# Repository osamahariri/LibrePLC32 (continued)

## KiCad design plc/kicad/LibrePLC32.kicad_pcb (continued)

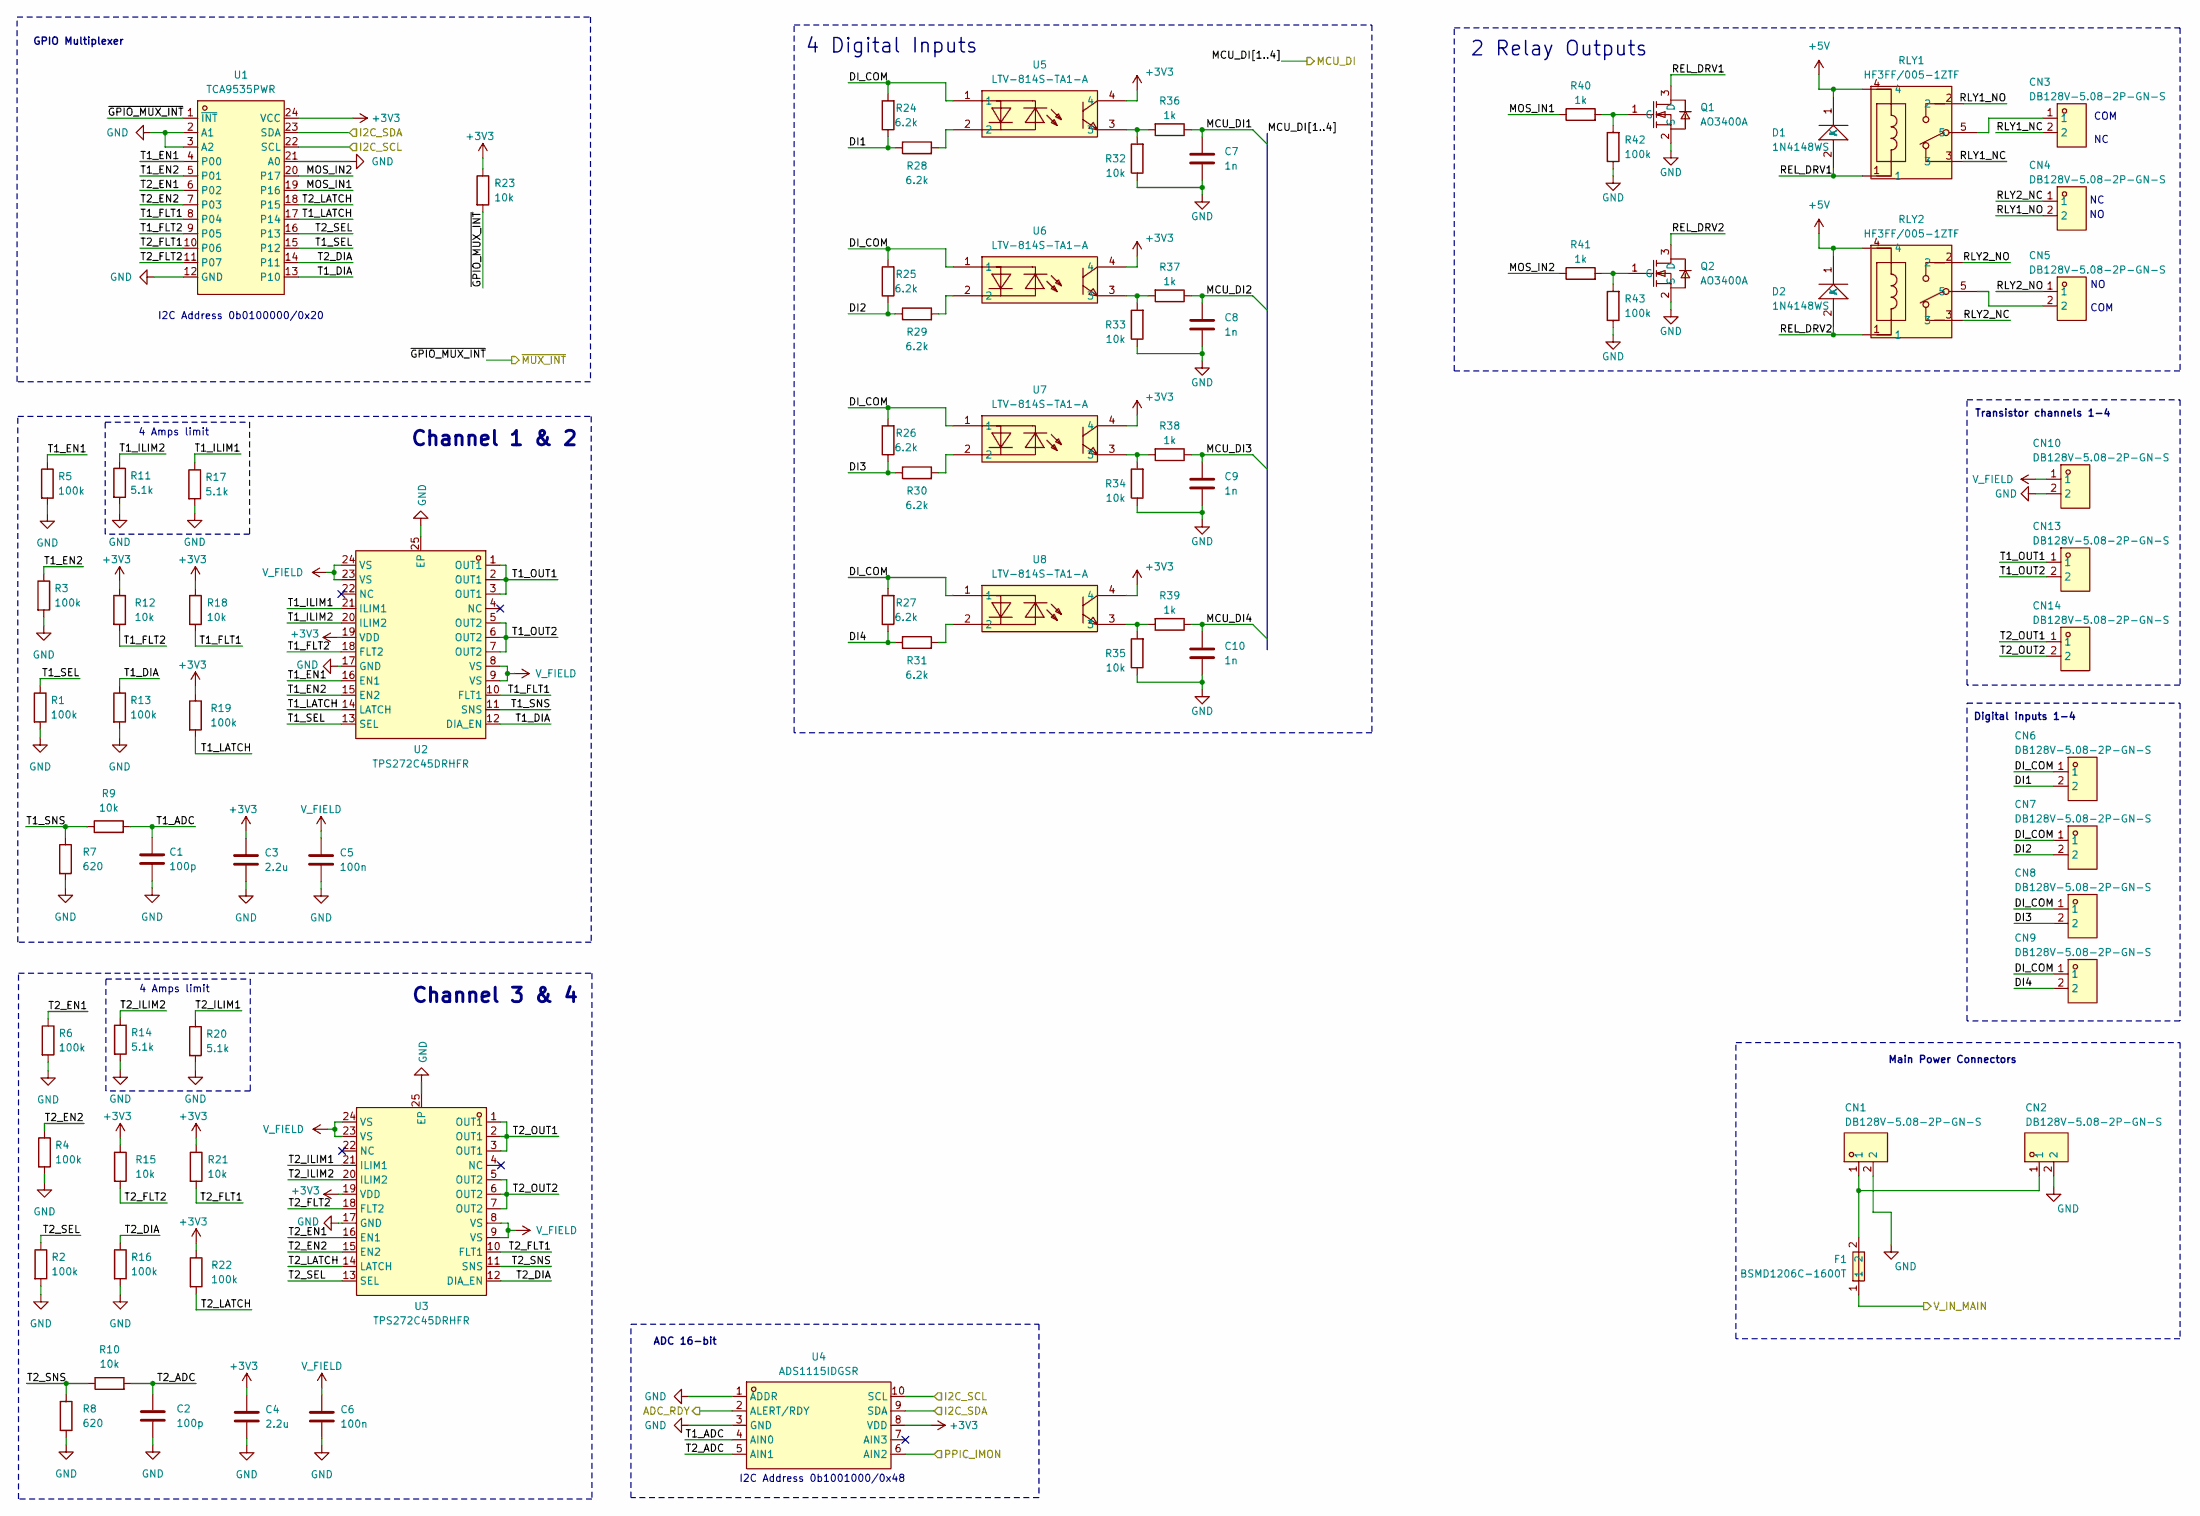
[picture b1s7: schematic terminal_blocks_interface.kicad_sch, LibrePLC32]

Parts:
C1, C2: 100p; C_0603_1608Metric
C3, C4: 2.2u; C_0603_1608Metric
C5, C6: 100n; C_0603_1608Metric
C7, C8, C9, C10: 1n; C_0603_1608Metric
CN1, CN2, CN3, CN4, CN5, CN6, CN7, CN8, CN9, CN10, CN13, CN14: DB128V-5.08-2P-GN-S; CONN-TH_2P-P5.08_DIBO_DB128V-5.08; MPN DB128V-5.08-2P-GN-S; LCSC Part C2915639
D1, D2: 1N4148WS; SOD-323_L1.8-W1.3-LS2.7-RD; MPN 1N4148WS-E3-08; LCSC Part C129905
F1: BSMD1206C-1600T; F1206; MPN BSMD1206C-1600T; LCSC Part C49328461
Q1, Q2: AO3400A; SOT-23-3_L2.9-W1.3-P1.90-LS2.4-BR; MPN AO3400A; LCSC Part C42419946
R1, R2, R3, R4, R5, R6, R13, R16, R19, R22, R42, R43: 100k; R_0603_1608Metric
R7, R8: 620; R_0603_1608Metric
R9, R10, R12, R15, R18, R21, R23, R32, R33, R34, R35: 10k; R_0603_1608Metric
R11, R14, R17, R20: 5.1k; R_0603_1608Metric
R24, R25, R26, R27, R28, R29, R30, R31: 6.2k; R_0603_1608Metric
R36, R37, R38, R39, R40, R41: 1k; R_0603_1608Metric
RLY1, RLY2: HF3FF/005-1ZTF; RELAY-TH_HF3FF-018-1ZT; MPN HF3FF/005-1ZTF; LCSC Part C2764967
U1: TCA9535PWR; TSSOP-24_L7.8-W4.4-P0.65-LS6.4-BL; MPN TCA9535PWR(UMW); LCSC Part C22396388
U2, U3: TPS272C45DRHFR; VQFN-24_L5.0-W4.0-P0.50-BL-EP-1; MPN TPS272C45DRHFR; LCSC Part C3219943
U4: ADS1115IDGSR; MSOP-10_L3.0-W3.0-P0.50-LS5.0-BL; MPN ADS1115IDGSR; LCSC Part C37593
U5, U6, U7, U8: LTV-814S-TA1-A; OPTO-SMD-4_L4.6-W6.5-P2.54-LS10.3-BL; MPN LTV-814S-TA1-A; LCSC Part C108051

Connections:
+3V3: C3.1, C4.1, R12.1, R15.1, R18.1, R19.1, R21.1, R22.1, R23.1, U1.24 (VCC), U2.19 (VDD), U3.19 (VDD), U4.8 (VDD), U5.4, U6.4, U7.4, U8.4; also elsewhere on the board
+5V: D1.1 (K), D2.1 (K), RLY1.4, RLY2.4; also elsewhere on the board
/MCU/ADC_RDY: U4.2 (ALERT/RDY); also elsewhere on the board
/MCU/I2C_SCL: U1.22 (SCL), U4.10 (SCL); also elsewhere on the board
/MCU/I2C_SDA: U1.23 (SDA), U4.9 (SDA); also elsewhere on the board
/MCU/MCU_DI1: C7.1, R36.1; also elsewhere on the board
/MCU/MCU_DI2: C8.1, R37.1; also elsewhere on the board
/MCU/MCU_DI3: C9.1, R38.1; also elsewhere on the board
/MCU/MCU_DI4: C10.1, R39.1; also elsewhere on the board
/Power/PPIC_IMON: U4.6 (AIN2); also elsewhere on the board
/Power/V_IN_MAIN: F1.1; also elsewhere on the board
/Terminal Blocks Interface/DI1: CN6.2, R24.1, R28.1
/Terminal Blocks Interface/DI2: CN7.2, R25.1, R29.1
/Terminal Blocks Interface/DI3: CN8.2, R26.1, R30.1
/Terminal Blocks Interface/DI4: CN9.2, R27.1, R31.1
/Terminal Blocks Interface/DI_COM: CN6.1, CN7.1, CN8.1, CN9.1, R24.2, R25.2, R26.2, R27.2, U5.1, U6.1, U7.1, U8.1
/Terminal Blocks Interface/MOS_IN1: R40.1, U1.19 (P16)
/Terminal Blocks Interface/MOS_IN2: R41.1, U1.20 (P17)
/Terminal Blocks Interface/REL_DRV1: D1.2 (A), Q1.3 (D), RLY1.1
/Terminal Blocks Interface/REL_DRV2: D2.2 (A), Q2.3 (D), RLY2.1
/Terminal Blocks Interface/RLY1_NC: CN3.2, RLY1.3
/Terminal Blocks Interface/RLY1_NO: CN4.2, RLY1.2
/Terminal Blocks Interface/RLY2_NC: CN4.1, RLY2.3
/Terminal Blocks Interface/RLY2_NO: CN5.1, RLY2.2
/Terminal Blocks Interface/T1_ADC: C1.1, R9.2, U4.4 (AIN0)
/Terminal Blocks Interface/T1_DIA: R13.1, U1.13 (P10), U2.12 (DIA_EN)
/Terminal Blocks Interface/T1_EN1: R5.1, U1.4 (P00), U2.16 (EN1)
/Terminal Blocks Interface/T1_EN2: R3.1, U1.5 (P01), U2.15 (EN2)
/Terminal Blocks Interface/T1_FLT1: R18.2, U1.8 (P04), U2.10 (FLT1)
/Terminal Blocks Interface/T1_FLT2: R12.2, U1.9 (P05), U2.18 (FLT2)
/Terminal Blocks Interface/T1_ILIM1: R17.1, U2.21 (ILIM1)
/Terminal Blocks Interface/T1_ILIM2: R11.1, U2.20 (ILIM2)
/Terminal Blocks Interface/T1_LATCH: R19.2, U1.17 (P14), U2.14 (LATCH)
/Terminal Blocks Interface/T1_OUT1: CN13.1, U2.1 (OUT1), U2.2 (OUT1), U2.3 (OUT1)
/Terminal Blocks Interface/T1_OUT2: CN13.2, U2.5 (OUT2), U2.6 (OUT2), U2.7 (OUT2)
/Terminal Blocks Interface/T1_SEL: R1.1, U1.15 (P12), U2.13 (SEL)
/Terminal Blocks Interface/T1_SNS: R7.1, R9.1, U2.11 (SNS)
/Terminal Blocks Interface/T2_ADC: C2.1, R10.2, U4.5 (AIN1)
/Terminal Blocks Interface/T2_DIA: R16.1, U1.14 (P11), U3.12 (DIA_EN)
/Terminal Blocks Interface/T2_EN1: R6.1, U1.6 (P02), U3.16 (EN1)
/Terminal Blocks Interface/T2_EN2: R4.1, U1.7 (P03), U3.15 (EN2)
/Terminal Blocks Interface/T2_FLT1: R21.2, U1.10 (P06), U3.10 (FLT1)
/Terminal Blocks Interface/T2_FLT2: R15.2, U1.11 (P07), U3.18 (FLT2)
/Terminal Blocks Interface/T2_ILIM1: R20.1, U3.21 (ILIM1)
/Terminal Blocks Interface/T2_ILIM2: R14.1, U3.20 (ILIM2)
/Terminal Blocks Interface/T2_LATCH: R22.2, U1.18 (P15), U3.14 (LATCH)
/Terminal Blocks Interface/T2_OUT1: CN14.1, U3.1 (OUT1), U3.2 (OUT1), U3.3 (OUT1)
/Terminal Blocks Interface/T2_OUT2: CN14.2, U3.5 (OUT2), U3.6 (OUT2), U3.7 (OUT2)
/Terminal Blocks Interface/T2_SEL: R2.1, U1.16 (P13), U3.13 (SEL)
/Terminal Blocks Interface/T2_SNS: R8.1, R10.1, U3.11 (SNS)
/Terminal Blocks Interface/~GPIO_MUX_INT: R23.2, U1.1 (~INT); also elsewhere on the board
GND: C1.2, C2.2, C3.2, C4.2, C5.2, C6.2, C7.2, C8.2, C9.2, C10.2, CN1.2, CN2.2, CN10.2, Q1.2 (S), Q2.2 (S), R1.2, R2.2, R3.2, R4.2, R5.2, R6.2, R7.2, R8.2, R11.2, R13.2, R14.2, R16.2, R17.2, R20.2, R32.1, R33.1, R34.1, R35.1, R42.1, R43.1, U1.2 (A1), U1.3 (A2), U1.12 (GND), U1.21 (A0), U2.17 (GND), U2.25 (EP), U3.17 (GND), U3.25 (EP), U4.1 (ADDR), U4.3 (GND); also elsewhere on the board
unnamed: CN1.1, CN2.1, F1.2
unnamed: CN3.1, RLY1.5
unnamed: CN5.2, RLY2.5
unnamed: Q1.1 (G), R40.2, R42.2
unnamed: Q2.1 (G), R41.2, R43.2
unnamed: R28.2, U5.2
unnamed: R29.2, U6.2
unnamed: R30.2, U7.2
unnamed: R31.2, U8.2
unnamed: R32.2, R36.2, U5.3
unnamed: R33.2, R37.2, U6.3
unnamed: R34.2, R38.2, U7.3
unnamed: R35.2, R39.2, U8.3
V_FIELD: C5.1, C6.1, CN10.1, U2.8 (VS), U2.9 (VS), U2.23 (VS), U2.24 (VS), U3.8 (VS), U3.9 (VS), U3.23 (VS), U3.24 (VS); also elsewhere on the board

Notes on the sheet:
ADC 16-bit
I2C Address 0b0100000/0x20
2 Relay Outputs
I2C Address 0b1001000/0x48
4 Amps limit
4 Digital Inputs
Transistor channels 1-4
GPIO Multiplexer
Channel 1 & 2
COM NC
Digital inputs 1-4
Main Power Connectors
NO COM
Channel 3 & 4

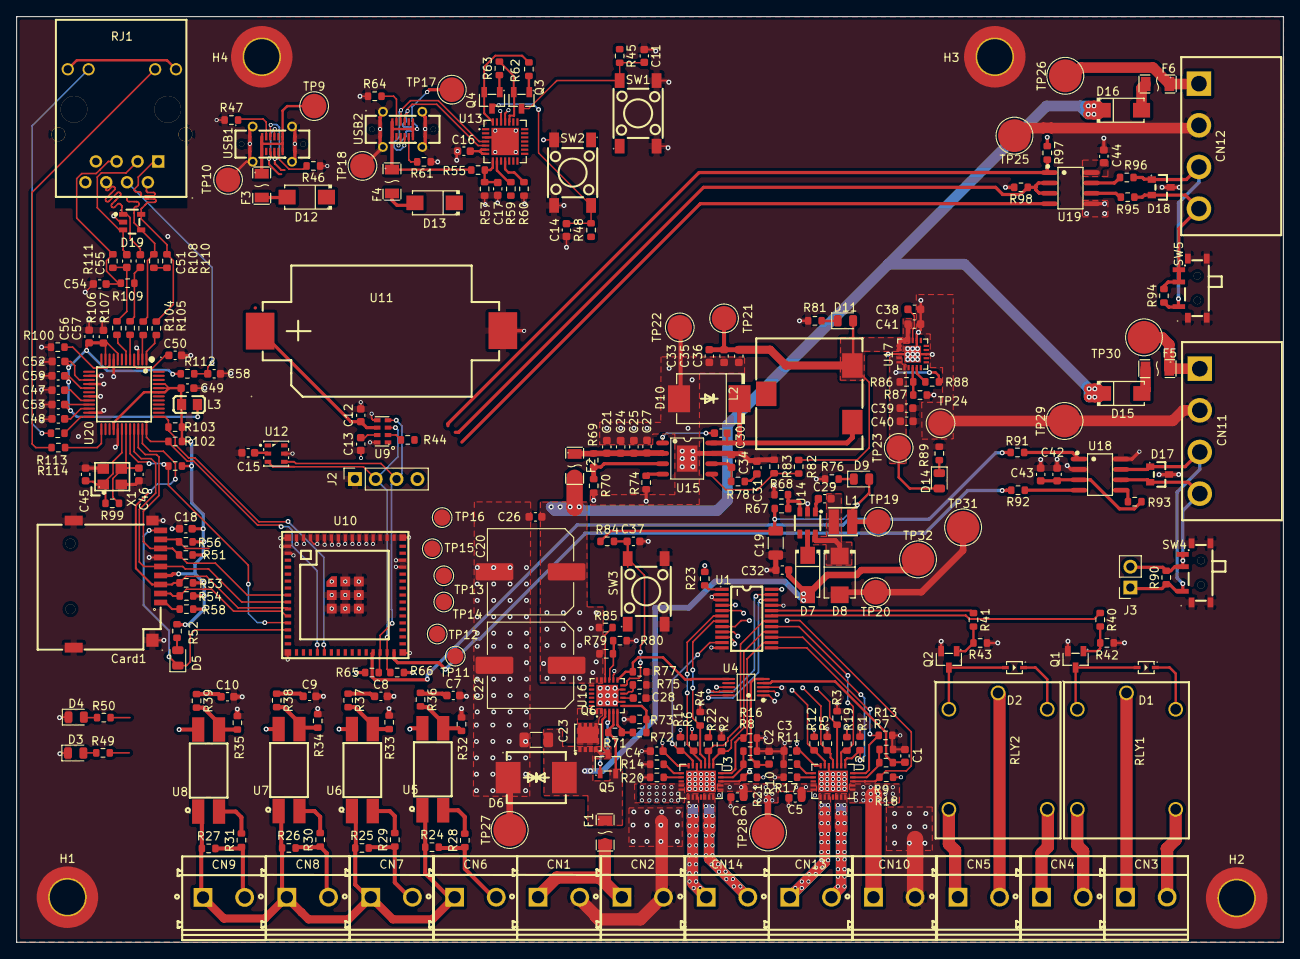
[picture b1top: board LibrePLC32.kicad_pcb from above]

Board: 4 copper layers, 154.5 x 112.9 mm, 283 parts (0 on the bottom side), 181 nets.

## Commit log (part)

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2026-04-27 Added microSD card
2026-04-27 Corrected TVS duplicated
2026-04-28 Added setup leds & shared SPI bus
2026-04-28 Fixed ADC pins & rc filter
2026-04-29 TPS54560 changed to TPS54560B
2026-04-29 Modified TPS26630 resistor values
2026-04-29 Changed TLV76733 to TPS7A52-Q1
2026-04-29 Updated LMR16006X circuit
2026-04-29 Removed CAN FLT resistor
2026-04-29 Added more wiring
2026-04-30 Eliminated series diode to output transistors
2026-04-30 Added TPS54560 PCB placement
2026-04-30 LMR16006X PCB placement
2026-04-30 TPS26630 PCB placement
2026-04-30 TPS7A52-Q1 PCB placement
2026-05-03 Updated W5500 to reference schematic
2026-05-03 Updated W5500 PCB Placement
2026-05-03 SD Card PCB Placement
2026-05-03 PCB placement of USB circuits
2026-05-03 Rearranged small PCB placements
2026-05-03 TPS272C45 PCB placement
2026-05-04 PCB placement updates
2026-05-05 Updated PCB placement
2026-05-06 Added mounting holes & PCB outline
2026-05-06 Updated switch placement for can & rs485
2026-05-07 DRC checks pass
2026-05-07 Updated PCB placement & graphics
2026-05-07 Added images
2026-05-07 Added logo on PCB
2026-05-07 Minor additions
2026-05-08 Added visual markers
2026-05-08 Readded OSHW Logo
2026-05-08 Added KiCAD logo on PCB
2026-05-08 Changed license to CERN-OHL-P
2026-05-08 Added 3D model of the board
2026-05-08 Fixed 3D model
2026-05-12 Added exclusion zone under relays
2026-05-17 Fixed shorting resistors for CAN & RS485
2026-06-05 Modified USB & RTC placement
2026-06-05 Changed CAN & RS485 to input voltage unprotected
2026-06-10 Tuned USB to 90ohms
2026-06-10 Updated SMD fuses to fuse holders
2026-06-11 Modified 3V3 aux to zener
2026-06-11 Reannotated schematic
2026-06-11 Silkscreen fixes
2026-06-11 Added isolated CAN bus
2026-06-11 Added isolated RS-485
2026-06-12 Routed Ethernet at 100 ohms
2026-06-12 Slight silkscreen & component adjustment
2026-06-15 Added more mounting holes
2026-06-15 Added amperage to silkscreen of fuse holders
2026-06-15 BOM Consolidation
    - CP2102N Vdbg divider: 22.1k→5.1k, 47.5k→10k (gives 3.29V)
    - I²C pull-ups (R65,R66): 4.7k→5.1k (verified ok)
    - Buck UVLO (R69,R70): 442k→100k, 90.9k→2×10k (UVLO = 7V)
    - TPS272C45D ILIM (R75): 3k→3×10k (~6A limit)
    - PPIC IMON + ETH_EXPRESS (R77,R100): 12.4k→2×6.2k
    - Buck compensation (R78): 16.9k→10k+6.2k+620 series
2026-06-15 BOM consolidation
    Consolidated two more resistor values
2026-06-15 Hidden mounting hole IDs
2026-06-15 Small modifications
2026-06-15 Modified PPIC_PGOOD to 100k
2026-06-16 Added fuse info
